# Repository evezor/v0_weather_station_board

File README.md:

# weather_station_board
*please note this board is has been deprecated.

This board uses the Evezor Stamp STMF405 MCU

source: https://github.com/evezor/Evezor-Stamp-STMF405

This weather station board features a barometric pressure sensor, an ambient light sensor and a temerature and humidity sensor. 

Evezor® and all associated marks, logos, and designs are registered trademarks and protected by copyright. Unauthorized use or reproduction of these trademarks and copyrighted materials is strictly prohibited

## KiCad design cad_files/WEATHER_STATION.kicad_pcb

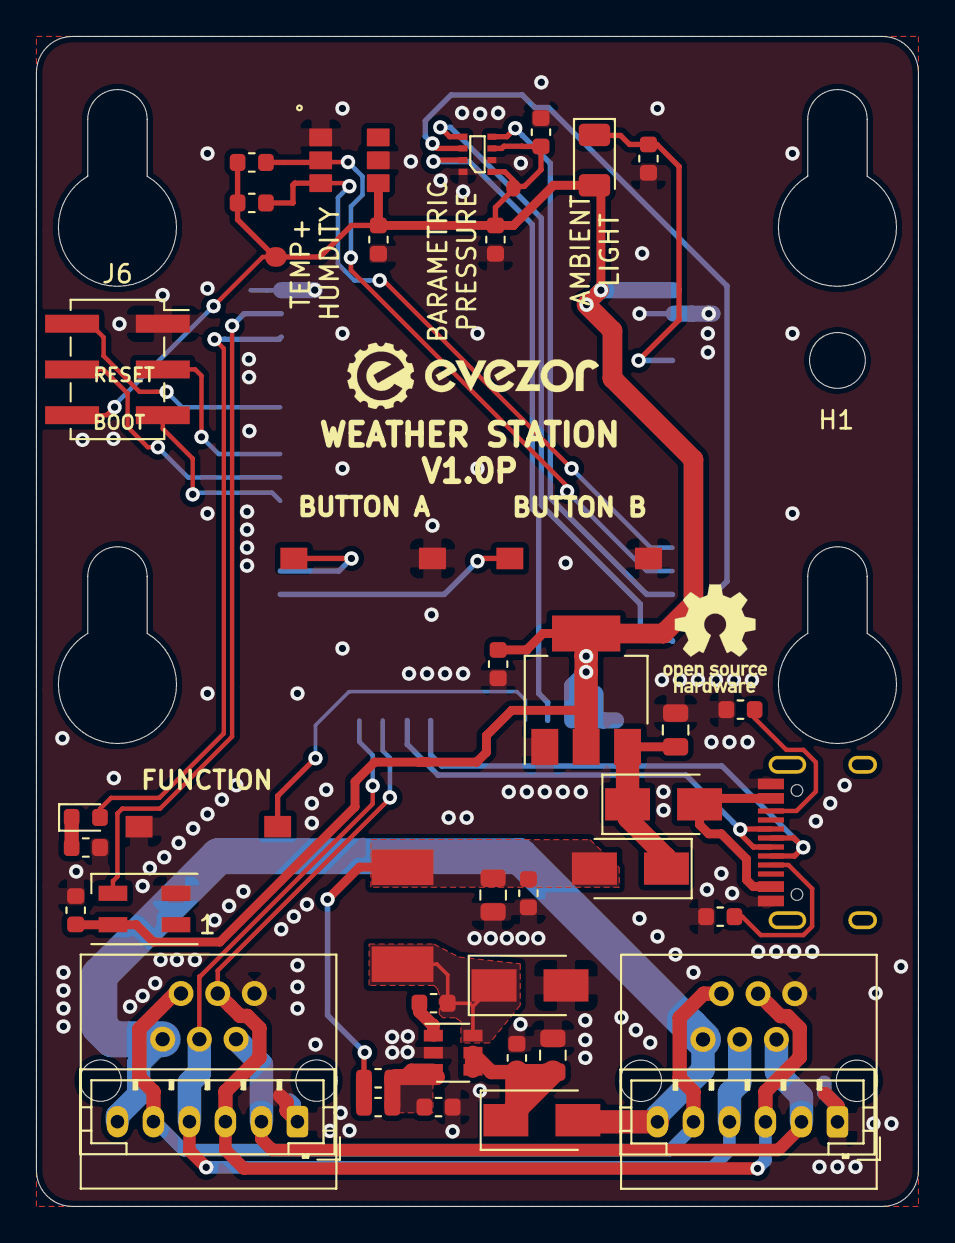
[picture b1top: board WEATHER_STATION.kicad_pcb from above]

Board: 2 copper layers, 49.0 x 65.0 mm, 43 parts (1 on the bottom side), 35 nets.

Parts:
C1, C2, C3, C5, C10, C11, C12, C13: .1uF; C_0603_1608Metric
C4: 4.7uF; C_0805_2012Metric
C6: 22uF; C_0805_2012Metric
C8: 10uF; C_0805_2012Metric
C9: C_Small; C_0603_1608Metric
D1, D2, D4, D5: SX35_SCHOTTKY; D_SMA
D3: LED; LED_0603_1608Metric
D6: SK6812MINI; LED_SK6812MINI_PLCC4_3.5x3.5mm_P1.75mm
D7: 1206-PTSM; LED_1206_3216Metric
H1: MountingHole; OLED_STANDOFF
J1: USB_C_Receptacle_USB2.0; USB_C_Receptacle_HRO_TYPE-C-31-M-12
J2, J3: RJ11; RJ11_C189747_Horizontal
J4, J5: PH; JST_PH_B6B-PH-K_1x06_P2.00mm_Vertical
J6: Conn_02x03_Odd_Even; OLED_HEADER
L1: 22uH; INDUCTOR_7.5X6.6_GCDA0630-220MC
R1, R5: 15k; R_0603_1608Metric
R2: 82k; R_0603_1608Metric
R3, R4: 5.1k; R_0603_1608Metric
R8: 1k; R_0603_1608Metric
R9, R10: 4.7k; R_0603_1608Metric
SW1, SW2, SW3: SW_Push; SWITCH_2x3_SMD_TACTILE_GREEN
U1: SY8401ABC; SOT-23-6
U2: AMS1117-3.3; SOT-223-3_TabPin2
U3: EDGE_STM32F405_CPU_V1; EDGE_STAMP
U5: SENSOR_TEMP+HUMIDITY_AHT10
U6: BMP280; BOSCH_BMP280_PRESSURE_ALTIMETER

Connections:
+3V3: C9.2, C10.1, C11.1, C12.1, C13.1, D6.4, D7.2, J6.6, R9.1, R10.1, U2.2, U3.1, U3.18, U5.4, U6.6, U6.8
/AMBIENT_LIGHT: D7.1, R8.2, U3.4
/BOOT: J6.3, U3.36
/BUTTON_A: SW2.1, U3.31
/BUTTON_B: SW3.1, U3.30
/CAN_H: J2.3, J3.3, J4.3, J5.3, U3.26
/CAN_L: J2.4, J3.4, J4.4, J5.4, U3.27
/CC1: J1.A5, R4.1
/CC2: J1.B5, R3.1
/CSEL: U3.19, U6.2
/D+: J1.A6, J1.B6, U3.25
/D-: J1.A7, J1.B7, U3.24
/FD_H: J2.2, J3.2, J4.2, J5.2
/FD_L: J2.5, J3.5, J4.5, J5.5
/FUNCTION_BUTTON: SW1.1, U3.20
/HBT_LED: D3.2, U3.41
/MISO: U3.14, U6.5
/MOSI: U3.15, U6.3
/NEO_STATUS: D6.3, U3.42
/OLED_SCL: J6.5, U3.34
/OLED_SDA: J6.4, U3.35
/RESET: J6.2, U3.38
/SCK: U3.16, U6.4
/SCL: R10.2, U3.12, U5.3
/SDA: R9.2, U3.13, U5.2
/USB_VCC: D4.2, J1.A4, J1.A9, J1.B4, J1.B9
/VREG_OUT: C2.1, C5.1, C6.1, D5.2, L1.2, R2.1
GND: C3.2, C4.2, C5.2, C6.2, C8.2, C9.1, C10.2, C11.2, C12.2, C13.2, D1.2, D6.2, J1.A1, J1.A12, J1.B1, J1.B12, J2.1, J3.1, J4.1, J5.1, J6.1, R1.1, R3.2, R4.2, R5.1, R8.1, SW1.2, SW2.2, SW3.2, U1.2, U2.1, U3.2, U3.17, U3.43, U5.1, U5.5, U6.1, U6.7
unnamed: C1.1, D1.1, L1.1, U1.6
unnamed: C1.2, U1.1
unnamed: C2.2, R1.2, R2.2, U1.3
unnamed: C3.1, C4.1, D2.1, U1.4, U1.5
unnamed: C8.1, D4.1, D5.1, U2.3
unnamed: D3.1, R5.2
VBUS: D2.2, J2.6, J3.6, J4.6, J5.6

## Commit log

2020-11-17 wake up can chip
2020-11-17 add datasheets
2020-11-18 add schematic
2023-09-11 Create LICENCE
2023-09-11 add pics
